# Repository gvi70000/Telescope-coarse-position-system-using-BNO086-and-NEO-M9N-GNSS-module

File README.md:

This article presents the hardware used for the coarse position of a motorized telescope.

The position is given by the onboard 9 axis IMU BNO086 on I2C bus, the position on Earth is determined using NEO-M9N GNSS module on UART.

For astronomical calculation the pressure and temperature of the environment is read using BMP581 pressure and temperature sensor.

The communication with the telescope main controller is done on RS485 using ST485EBDR RS232 to RS485 converter and the level shifting between

3.3V and 5V is done using TXS0104E level shifter.

This device comes equipped also with 64kbyte SPI EEPROM to store user data.

The KiCAD files can be downloaded here.

The C library software for each IC are uploaded in this repository.

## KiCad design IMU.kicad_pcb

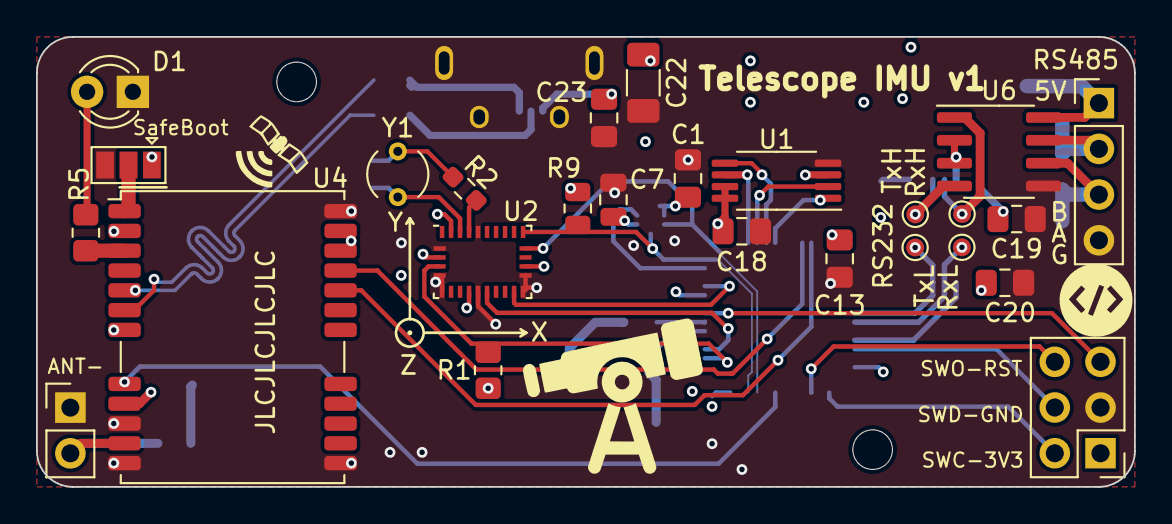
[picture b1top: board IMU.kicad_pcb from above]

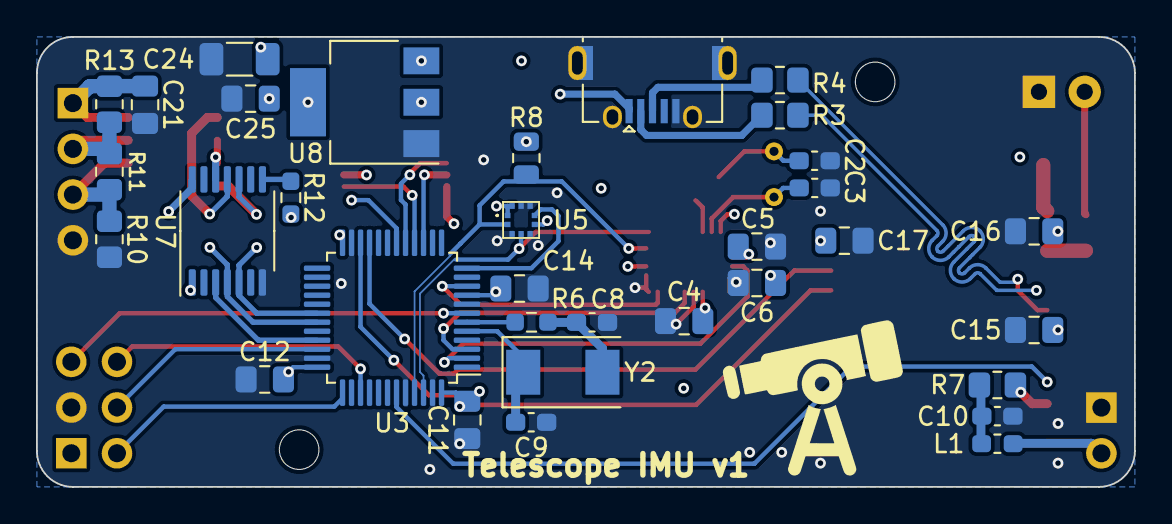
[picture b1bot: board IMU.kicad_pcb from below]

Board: 4 copper layers, 61.0 x 25.0 mm, 61 parts (33 on the bottom side), 46 nets.

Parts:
C1, C4, C5, C6, C11, C12, C13, C14, C15, C16, C17, C18, C19, C20, C21, C23, C25: 100n; C_0805_2012Metric_Pad1.18x1.45mm_HandSolder
C2, C3: 22p; C_0603_1608Metric_Pad1.08x0.95mm_HandSolder
C7: 100n; C_0805_2012Metric
C8, C9: 18p; C_0603_1608Metric_Pad1.08x0.95mm_HandSolder
C10: 100n; C_0603_1608Metric_Pad1.08x0.95mm_HandSolder
C22, C24: 10u; C_1206_3216Metric_Pad1.33x1.80mm_HandSolder
D1: LED; LED_D3.0mm
H1, H2: MountingHole; MountingHole_2.2mm_M2
J1: Conn_01x02; PinHeader_1x02_P2.54mm_Vertical
J2: Conn_01x04; PinHeader_1x04_P2.54mm_Vertical
J3: USB_B_Micro; USB_Micro-AB_Molex_47590-0001
JP1: Jumper_3_Open; SolderJumper-3_P1.3mm_Open_Pad1.0x1.5mm
L1: 27nH; L_0603_1608Metric_Pad1.05x0.95mm_HandSolder
PRG1: Conn_02x03_Counter_Clockwise; PinHeader_2x03_P2.54mm_Vertical
R1: 10k; R_0805_2012Metric_Pad1.20x1.40mm_HandSolder
R2, R6: 1k; R_0603_1608Metric_Pad0.98x0.95mm_HandSolder
R3, R4: 27; R_0805_2012Metric_Pad1.20x1.40mm_HandSolder
R5, R10, R13: 1k; R_0805_2012Metric_Pad1.20x1.40mm_HandSolder
R7: 10; R_0805_2012Metric_Pad1.20x1.40mm_HandSolder
R8, R9: 2.2k; R_0805_2012Metric
R11: 220; R_0805_2012Metric_Pad1.20x1.40mm_HandSolder
R12: 10k; R_0603_1608Metric_Pad0.98x0.95mm_HandSolder
RX1, RX2: TestPoint; TestPoint_Pad_D1.0mm
TX1, TX2: TestPoint; TestPoint_Pad_D1.0mm
U1: M95256-WMN6P; TSSOP-8_4.4x3mm_P0.65mm
U2: BNO055; LGA-28_5.2x3.8mm_P0.5mm
U3: STM32F302C6Tx; LQFP-48_7x7mm_P0.5mm
U4: NEO-M9N; ublox_NEO
U5: BMP581
U6: ST485EBDR; SOIC-8_3.9x4.9mm_P1.27mm
U7: TXS0104E; TSSOP-14_4.4x5mm_P0.65mm
U8: LD1117; SOT-223-3_TabPin2
Y1: Crystal; Crystal_AT310_D3.0mm_L10.0mm_Vertical
Y2: 8MHz; Crystal_SMD_0603-2Pin_6.0x3.5mm

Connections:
+3V3: C1.1, C5.1, C6.1, C7.1, C11.1, C12.1, C13.1, C14.1, C15.1, C16.1, C17.1, C18.1, C20.1, C24.1, C25.1, JP1.1 (A), PRG1.1, R1.1, R8.2, R9.2, R12.2, U1.3 (~W), U1.7 (~HOLD), U1.8 (VCC), U2.3 (VDD), U2.17 (COM3), U2.28 (VDDIO), U3.9 (VDDA), U3.24 (VDD), U3.36 (VDD), U3.48 (VDD), U4.2 (D_SEL), U4.7 (VDD_USB), U4.22 (V_BCKP), U4.23 (VCC), U5.1 (VDDIO), U5.6 (CSB), U5.10 (VDD), U7.1 (VCCA), U8.2 (VO)
+5V: C19.1, C21.1, C22.1, C23.1, J2.1, J3.1 (VBUS), R13.1, U6.8 (VCC), U7.14 (VCCB), U8.3 (VI)
A: J2.3, R10.1, R11.2, U6.6 (A)
B: J2.2, R11.1, R13.2, U6.7 (B)
BMP_INT: U3.12 (PA2), U5.7 (INT)
BNO_BOOT: R1.2, U2.4 (~BOOT_LOAD_PIN), U3.2 (PC13)
BNO_INT: U2.14 (INT), U3.10 (PA0)
BNO_RST: U2.11 (~RESET), U3.3 (PC14)
CS_MEM: U1.1 (~S), U3.18 (PB0)
D+: J3.3 (D+), R4.1
D-: J3.2 (D-), R3.1
DE_H: U6.2 (~RE), U6.3 (DE), U7.12 (B2)
DE_L: U3.33 (PA12), U7.3 (A2)
GND: C1.2, C2.2, C3.2, C4.2, C5.2, C6.2, C7.2, C8.2, C9.2, C10.1, C11.2, C12.2, C13.2, C14.2, C15.2, C16.2, C17.2, C18.2, C19.2, C20.2, C21.2, C22.2, C23.2, C24.2, C25.2, D1.1 (K), J1.1, J2.4, J3.5 (GND), J3.6 (Shield), JP1.3 (B), PRG1.3, R10.2, U1.4 (VSS), U2.2 (GND), U2.5 (PS1), U2.6 (PS0), U2.10 (BL_IND), U2.15 (GNDIO), U2.16 (GNDIO), U2.25 (GNDIO), U3.8 (VSSA), U3.23 (VSS), U3.35 (VSS), U3.44 (BOOT0), U3.47 (VSS), U4.10 (GND), U4.12 (GND), U4.13 (GND), U4.24 (GND), U5.3 (VSS_1), U5.5 (SDO), U5.8 (VSS_2), U5.9 (VSS_3), U6.5 (GND), U7.7 (GND), U8.1 (GND)
GPS_ANT: J1.2, L1.1, U4.11 (RF_IN)
GPS_RST: U3.43 (PB7), U4.8 (~RESET)
GPS_RX: U3.21 (PB10), U4.21 (RXD/SPI_MOSI)
GPS_TX: U3.22 (PB11), U4.20 (TXD/SPI_MISO)
MISO: U1.2 (Q), U3.16 (PA6)
MOSI: U1.5 (D), U3.17 (PA7)
NRST: PRG1.5, U3.7 (NRST)
unnamed: C2.1, R2.1, Y1.2
unnamed: C8.1, R6.1, Y2.2
unnamed: C10.2, L1.2, R7.2
unnamed: D1.2 (A), R5.2
unnamed: JP1.2 (C), U4.1 (~SAFEBOOT)
unnamed: C4.1, U2.9 (CAP)
unnamed: C3.1, U2.27 (XIN32), Y1.1
unnamed: R2.2, U2.26 (XOUT32)
unnamed: R5.1, U4.3 (TIMEPULSE)
unnamed: R12.1, U7.8 (OE)
OSC_IN: C9.1, U3.5 (PF0), Y2.1
OSC_OUT: R6.2, U3.6 (PF1)
RX_H: RX2.1, U6.1 (RO), U7.11 (B3)
RX_L: RX1.1, U3.31 (PA10), U7.4 (A3)
SCK: U1.6 (C), U3.15 (PA5)
SCL: R8.1, U2.19 (COM1), U3.45 (PB8), U5.2 (SCK)
SDA: R9.1, U2.20 (COM0), U3.46 (PB9), U5.4 (SDI)
SWCLK: PRG1.2, U3.37 (PA14)
SWDIO: PRG1.4, U3.34 (PA13)
SWO: PRG1.6, U3.39 (PB3)
TX_H: TX2.1, U6.4 (DI), U7.10 (B4)
TX_L: TX1.1, U3.30 (PA9), U7.5 (A4)
USB_N: R3.2, U4.5 (USB_DM)
USB_P: R4.2, U4.6 (USB_DP)
VCC_RF: R7.1, U4.9 (VCC_RF)

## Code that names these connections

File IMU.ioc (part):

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Mcu.Name=STM32F302C(B-C)Tx
Mcu.Package=LQFP48
Mcu.UserName=STM32F302CCTx
PA0.GPIOParameters=GPIO_PuPd,GPIO_Label,GPIO_ModeDefaultEXTI
PA0.GPIO_Label=BNO_INT
PA0.GPIO_ModeDefaultEXTI=GPIO_MODE_IT_FALLING
PA0.GPIO_PuPd=GPIO_PULLUP
PA0.Signal=GPXTI0
PA10.Mode=Asynchronous
PA10.Signal=USART1_RX
PA12.Mode=Hardware Flow Control (RS485)
PA12.Signal=USART1_DE
PA13.Mode=Trace_Asynchronous_SW
PA13.Signal=SYS_JTMS-SWDIO
PA14.Mode=Trace_Asynchronous_SW
PA14.Signal=SYS_JTCK-SWCLK
PA2.GPIOParameters=GPIO_PuPd,GPIO_Label,GPIO_ModeDefaultEXTI
PA2.GPIO_Label=BMP_INT
PA2.GPIO_ModeDefaultEXTI=GPIO_MODE_IT_RISING
PA2.GPIO_PuPd=GPIO_PULLUP
PA2.Signal=GPXTI2
PA5.Mode=Full_Duplex_Master
PA5.Signal=SPI1_SCK
PA6.Mode=Full_Duplex_Master
PA6.Signal=SPI1_MISO
PA7.Mode=Full_Duplex_Master
PA7.Signal=SPI1_MOSI
PA9.Mode=Asynchronous
PA9.Signal=USART1_TX
PB0.GPIOParameters=PinState,GPIO_Label
PB0.GPIO_Label=CS_MEM
PB0.PinState=GPIO_PIN_SET
PB0.Signal=GPIO_Output
PB10.GPIOParameters=GPIO_Label
PB10.GPIO_Label=GPS_RX
PB10.Mode=Asynchronous
PB10.Signal=USART3_TX
PB11.GPIOParameters=GPIO_Label
PB11.GPIO_Label=GPS_TX
PB11.Mode=Asynchronous
PB11.Signal=USART3_RX
PB3.Mode=Trace_Asynchronous_SW
PB3.Signal=SYS_JTDO-TRACESWO
PB7.GPIOParameters=GPIO_Label
PB7.GPIO_Label=GPS_RST
PB7.Signal=GPIO_Output
PB8.Mode=I2C
PB8.Signal=I2C1_SCL
PB9.Mode=I2C
PB9.Signal=I2C1_SDA
PC13.GPIOParameters=PinState,GPIO_Label
PC13.GPIO_Label=BNO_BOOT
PC13.PinState=GPIO_PIN_SET
PC13.Signal=GPIO_Output
PC14-OSC32_IN.GPIOParameters=GPIO_Label
PC14-OSC32_IN.GPIO_Label=BNO_RST
PC14-OSC32_IN.Signal=GPIO_Output
PF0-OSC_IN.Mode=HSE-External-Oscillator
PF0-OSC_IN.Signal=RCC_OSC_IN
PF1-OSC_OUT.Mode=HSE-External-Oscillator
PF1-OSC_OUT.Signal=RCC_OSC_OUT
RCC.HSEPLLFreq_Value=8000000
RCC.HSE_VALUE=8000000
RCC.SYSCLKFreq_VALUE=72000000
RCC.SYSCLKSourceVirtual=RCC_SYSCLKSOURCE_PLLCLK
board=custom

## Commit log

2024-11-17 Add files via upload
    KiCAD project files (Schematic, board, manufacturing)
2024-11-17 Add files via upload
    Flex PCB for BMP581 and HDC3020
